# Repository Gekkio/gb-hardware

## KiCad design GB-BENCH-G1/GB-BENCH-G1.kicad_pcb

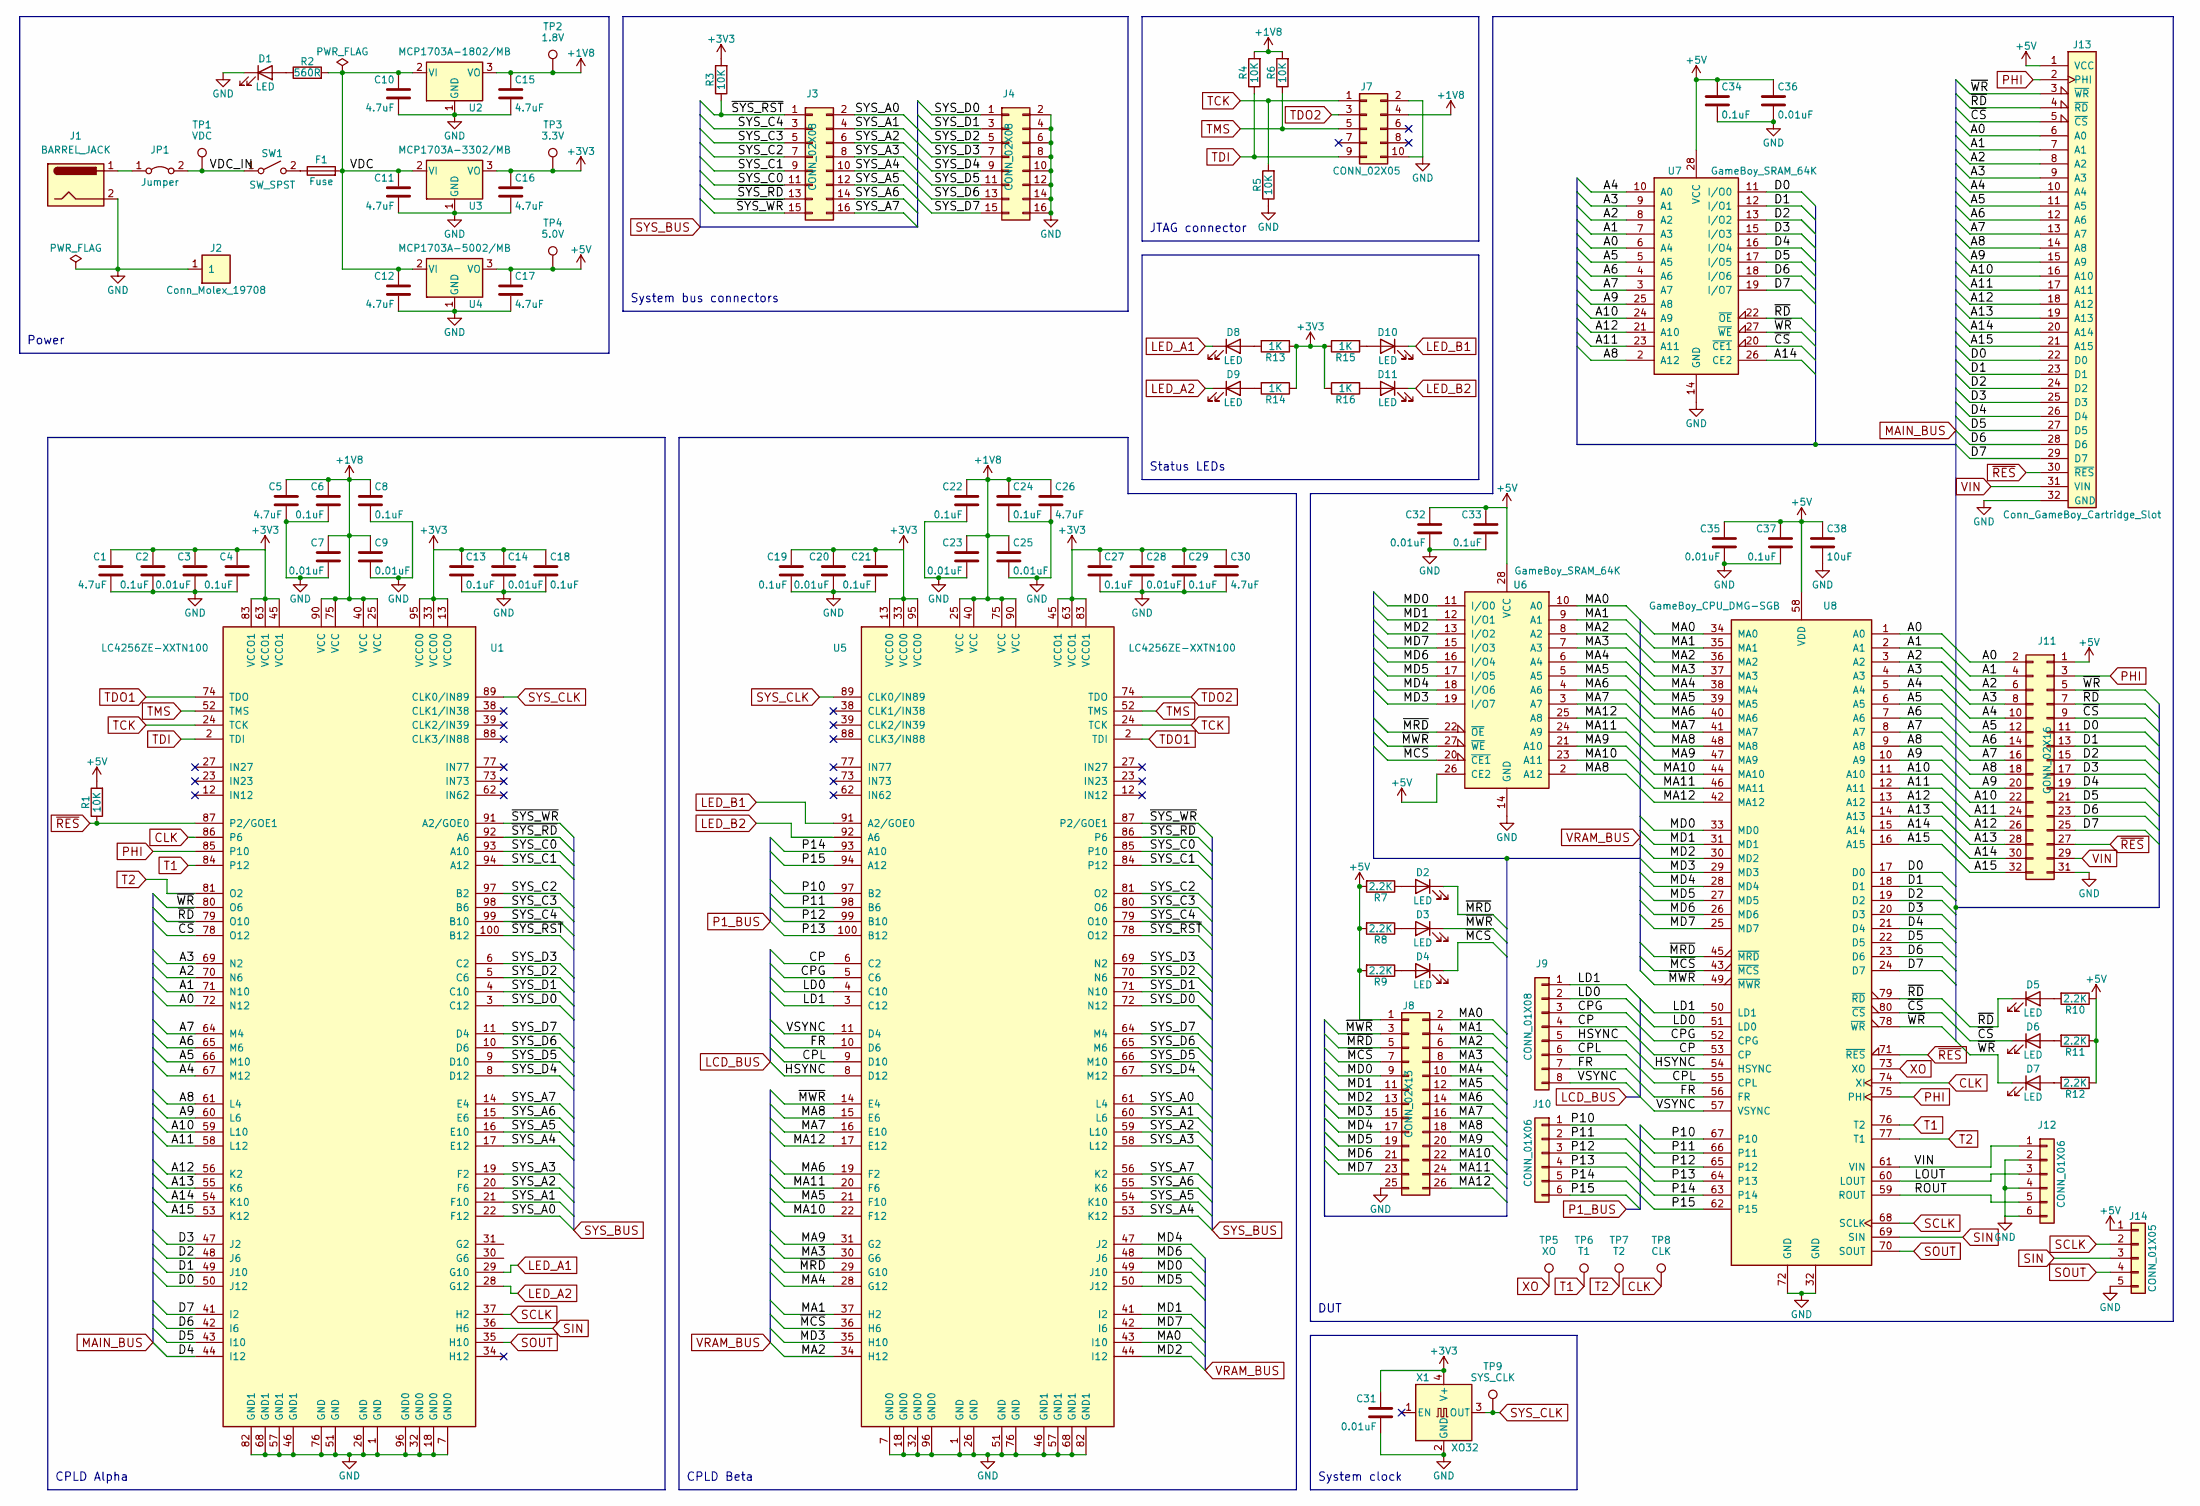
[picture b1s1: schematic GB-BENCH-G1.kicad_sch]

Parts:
C1, C5, C10, C11, C12, C15, C16, C17, C26, C30: 4.7uF; C_1206
C2, C4, C6, C8, C13, C18, C19, C21, C22, C24, C27, C29, C33, C34, C37: 0.1uF; C_0603
C3, C7, C9, C14, C20, C23, C25, C28, C31, C32, C35, C36: 0.01uF; C_0603
C38: 10uF; C_0805
D1: LED; LED_D3.0mm
D2, D3, D4, D5, D6, D7, D8, D9, D10, D11: LED; LED_0603
F1: Fuse; Fuse_SMD1206_Reflow
J1: BARREL_JACK; CUIInc_PJ-202A
J2: Conn_Molex_19708; Molex_19708-401X
J3, J4: CONN_02X08; IDC_Header_Straight_16pins
J7: CONN_02X05; Pin_Header_Straight_2x05_Pitch2.54mm
J8: CONN_02X13; Pin_Header_Straight_2x13_Pitch2.54mm
J9: CONN_01X08; Pin_Header_Straight_1x08_Pitch2.54mm
J10, J12: CONN_01X06; Pin_Header_Straight_1x06_Pitch2.54mm
J11: CONN_02X16; Pin_Header_Straight_2x16_Pitch2.54mm
J13: Conn_GameBoy_Cartridge_Slot; GameBoy_Cartridge_Slot_DSLite
J14: CONN_01X05; Pin_Header_Straight_1x05_Pitch2.54mm
JP1: Jumper; Pin_Header_Straight_1x02_Pitch2.54mm
R1, R3, R4, R5, R6: 10K; R_0603
R2: 560R; R_Axial_DIN0207_L6.3mm_D2.5mm_P7.62mm_Horizontal
R7, R8, R9, R10, R11, R12: 2.2K; R_0603
R13, R14, R15, R16: 1K; R_0603
SW1: SW_SPST; E-Switch_RA12131100
TP1: VDC; PINTST
TP2: 1.8V; PINTST
TP3: 3.3V; PINTST
TP4: 5.0V; PINTST
TP5: XO; PINTST
TP6: T1; PINTST
TP7: T2; PINTST
TP8: CLK; PINTST
TP9: SYS_CLK; PINTST
U1, U5: LC4256ZE-XXTN100; TQFP-100_14x14mm_Pitch0.5mm
U2: MCP1703A-1802/MB; SOT-89-3
U3: MCP1703A-3302/MB; SOT-89-3
U4: MCP1703A-5002/MB; SOT-89-3
U6, U7: GameBoy_SRAM_64K; SOP-28_8.6x18mm_Pitch1.27mm
U8: GameBoy_CPU_DMG-SGB; PQFP-80_14x20mm_Pitch0.8mm
X1: XO32; Oscillator_SMD_EuroQuartz_XO32-4pin_3.2x2.5mm

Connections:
+1V8: C5.1, C6.1, C7.1, C8.1, C9.1, C15.1, C22.1, C23.1, C24.1, C25.1, C26.1, J7.4, R4.2, R6.2, TP2.1, U1.25 (VCC), U1.40 (VCC), U1.75 (VCC), U1.90 (VCC), U2.3 (VO), U5.25 (VCC), U5.40 (VCC), U5.75 (VCC), U5.90 (VCC)
+3V3: C1.1, C2.1, C3.1, C4.1, C13.1, C14.1, C16.1, C18.1, C19.1, C20.1, C21.1, C27.1, C28.1, C29.1, C30.1, C31.1, R3.2, R13.1, R14.1, R15.1, R16.1, TP3.1, U1.13 (VCCO0), U1.33 (VCCO0), U1.45 (VCCO1), U1.63 (VCCO1), U1.83 (VCCO1), U1.95 (VCCO0), U3.3 (VO), U5.13 (VCCO0), U5.33 (VCCO0), U5.45 (VCCO1), U5.63 (VCCO1), U5.83 (VCCO1), U5.95 (VCCO0), X1.4 (V+)
+5V: C17.1, C32.1, C33.1, C34.1, C35.1, C36.1, C37.1, C38.1, J8.1, J11.1, J13.1 (VCC), J14.1, R1.2, R7.2, R8.2, R9.2, R10.1, R11.1, R12.1, TP4.1, U4.3 (VO), U6.26 (CE2), U6.28 (VCC), U7.28 (VCC), U8.58 (VDD)
/A0: J11.2, J13.6 (A0), U1.72 (N12), U7.6 (A4), U8.1 (A0)
/A1: J11.4, J13.7 (A1), U1.71 (N10), U7.7 (A3), U8.2 (A1)
/A2: J11.6, J13.8 (A2), U1.70 (N6), U7.8 (A2), U8.3 (A2)
/A3: J11.8, J13.9 (A3), U1.69 (N2), U7.9 (A1), U8.4 (A3)
/A4: J11.10, J13.10 (A4), U1.67 (M12), U7.10 (A0), U8.5 (A4)
/A5: J11.12, J13.11 (A5), U1.66 (M10), U7.5 (A5), U8.6 (A5)
/A6: J11.14, J13.12 (A6), U1.65 (M6), U7.4 (A6), U8.7 (A6)
/A7: J11.16, J13.13 (A7), U1.64 (M4), U7.3 (A7), U8.8 (A7)
/A8: J11.18, J13.14 (A8), U1.61 (L4), U7.2 (A12), U8.9 (A8)
/A9: J11.20, J13.15 (A9), U1.60 (L6), U7.25 (A8), U8.10 (A9)
/A10: J11.22, J13.16 (A10), U1.59 (L10), U7.24 (A9), U8.11 (A10)
/A11: J11.24, J13.17 (A11), U1.58 (L12), U7.23 (A11), U8.12 (A11)
/A12: J11.26, J13.18 (A12), U1.56 (K2), U7.21 (A10), U8.13 (A12)
/A13: J11.28, J13.19 (A13), U1.55 (K6), U8.14 (A13)
/A14: J11.30, J13.20 (A14), U1.54 (K10), U7.26 (CE2), U8.15 (A14)
/A15: J11.32, J13.21 (A15), U1.53 (K12), U8.16 (A15)
/CP: J9.4, U5.6 (C2), U8.53 (CP)
/CPG: J9.3, U5.5 (C6), U8.52 (CPG)
/CPL: J9.6, U5.9 (D10), U8.55 (CPL)
/D0: J11.11, J13.22 (D0), U1.50 (J12), U7.11 (I/O0), U8.17 (D0)
/D1: J11.13, J13.23 (D1), U1.49 (J10), U7.12 (I/O1), U8.18 (D1)
/D2: J11.15, J13.24 (D2), U1.48 (J6), U7.13 (I/O2), U8.19 (D2)
/D3: J11.17, J13.25 (D3), U1.47 (J2), U7.15 (I/O3), U8.20 (D3)
/D4: J11.19, J13.26 (D4), U1.44 (I12), U7.16 (I/O4), U8.21 (D4)
/D5: J11.21, J13.27 (D5), U1.43 (I10), U7.17 (I/O5), U8.22 (D5)
/D6: J11.23, J13.28 (D6), U1.42 (I6), U7.18 (I/O6), U8.23 (D6)
/D7: J11.25, J13.29 (D7), U1.41 (I2), U7.19 (I/O7), U8.24 (D7)
/FR: J9.7, U5.10 (D6), U8.56 (FR)
/HSYNC: J9.5, U5.8 (D12), U8.54 (HSYNC)
/LD0: J9.2, U5.4 (C10), U8.51 (LD0)
/LD1: J9.1, U5.3 (C12), U8.50 (LD1)
/LOUT: J12.3, U8.60 (LOUT)
/MA0: J8.2, U5.43 (I10), U6.10 (A0), U8.34 (MA0)
/MA1: J8.4, U5.37 (H2), U6.9 (A1), U8.35 (MA1)
/MA2: J8.6, U5.34 (H12), U6.8 (A2), U8.36 (MA2)
/MA3: J8.8, U5.30 (G6), U6.7 (A3), U8.37 (MA3)
/MA4: J8.10, U5.28 (G12), U6.6 (A4), U8.38 (MA4)
/MA5: J8.12, U5.21 (F10), U6.5 (A5), U8.39 (MA5)
/MA6: J8.14, U5.19 (F2), U6.4 (A6), U8.40 (MA6)
/MA7: J8.16, U5.16 (E10), U6.3 (A7), U8.41 (MA7)
/MA8: J8.18, U5.15 (E6), U6.2 (A12), U8.48 (MA8)
/MA9: J8.20, U5.31 (G2), U6.21 (A10), U8.47 (MA9)
/MA10: J8.22, U5.22 (F12), U6.23 (A11), U8.44 (MA10)
/MA11: J8.24, U5.20 (F6), U6.24 (A9), U8.46 (MA11)
/MA12: J8.26, U5.17 (E12), U6.25 (A8), U8.42 (MA12)
/MD0: J8.9, U5.49 (J10), U6.11 (I/O0), U8.33 (MD0)
/MD1: J8.11, U5.41 (I2), U6.12 (I/O1), U8.31 (MD1)
/MD2: J8.13, U5.44 (I12), U6.13 (I/O2), U8.30 (MD2)
/MD3: J8.15, U5.35 (H10), U6.19 (I/O7), U8.29 (MD3)
/MD4: J8.17, U5.47 (J2), U6.18 (I/O6), U8.28 (MD4)
/MD5: J8.19, U5.50 (J12), U6.17 (I/O5), U8.27 (MD5)
/MD6: J8.21, U5.48 (J6), U6.16 (I/O4), U8.26 (MD6)
/MD7: J8.23, U5.42 (I6), U6.15 (I/O3), U8.25 (MD7)
/P10: J10.1, U5.97 (B2), U8.67 (P10)
/P11: J10.2, U5.98 (B6), U8.66 (P11)
/P12: J10.3, U5.99 (B10), U8.65 (P12)
/P13: J10.4, U5.100 (B12), U8.64 (P13)
/P14: J10.5, U5.93 (A10), U8.63 (P14)
/P15: J10.6, U5.94 (A12), U8.62 (P15)
/ROUT: J12.5, U8.59 (ROUT)
/SYS_A0: J3.2, U1.22 (F12), U5.61 (L4)
/SYS_A1: J3.4, U1.21 (F10), U5.60 (L6)
/SYS_A2: J3.6, U1.20 (F6), U5.59 (L10)
/SYS_A3: J3.8, U1.19 (F2), U5.58 (L12)
/SYS_A4: J3.10, U1.17 (E12), U5.53 (K12)
/SYS_A5: J3.12, U1.16 (E10), U5.54 (K10)
/SYS_A6: J3.14, U1.15 (E6), U5.55 (K6)
/SYS_A7: J3.16, U1.14 (E4), U5.56 (K2)
/SYS_C0: J3.11, U1.93 (A10), U5.85 (P10)
/SYS_C1: J3.9, U1.94 (A12), U5.84 (P12)
/SYS_C2: J3.7, U1.97 (B2), U5.81 (O2)
/SYS_C3: J3.5, U1.98 (B6), U5.80 (O6)
/SYS_C4: J3.3, U1.99 (B10), U5.79 (O10)
/SYS_D0: J4.1, U1.3 (C12), U5.72 (N12)
/SYS_D1: J4.3, U1.4 (C10), U5.71 (N10)
/SYS_D2: J4.5, U1.5 (C6), U5.70 (N6)
/SYS_D3: J4.7, U1.6 (C2), U5.69 (N2)
/SYS_D4: J4.9, U1.8 (D12), U5.67 (M12)
/SYS_D5: J4.11, U1.9 (D10), U5.66 (M10)
/SYS_D6: J4.13, U1.10 (D6), U5.65 (M6)
/SYS_D7: J4.15, U1.11 (D4), U5.64 (M4)
/VDC: C10.1, C11.1, C12.1, F1.2, R2.2, U2.2 (VI), U3.2 (VI), U4.2 (VI)
/VDC_IN: JP1.2 (B), SW1.1 (A), TP1.1
/VSYNC: J9.8, U5.11 (D4), U8.57 (VSYNC)
/~CS: D6.1 (K), J11.9, J13.5 (~CS), U1.78 (O12), U7.20 (~CE1), U8.80 (~CS)
/~MCS: D4.1 (K), J8.7, U5.36 (H6), U6.20 (~CE1), U8.43 (~MCS)
/~MRD: D2.1 (K), J8.5, U5.29 (G10), U6.22 (~OE), U8.45 (~MRD)
/~MWR: D3.1 (K), J8.3, U5.14 (E4), U6.27 (~WE), U8.49 (~MWR)
/~RD: D5.1 (K), J11.7, J13.4 (~RD), U1.79 (O10), U7.22 (~OE), U8.79 (~RD)
/~SYS_RD: J3.13, U1.92 (A6), U5.86 (P6)
/~SYS_RST: J3.1, R3.1, U1.100 (B12), U5.78 (O12)
/~SYS_WR: J3.15, U1.91 (A2/GOE0), U5.87 (P2/GOE1)
/~WR: D7.1 (K), J11.5, J13.3 (~WR), U1.80 (O6), U7.27 (~WE), U8.78 (~WR)
CLK: TP8.1, U1.86 (P6), U8.74 (XI)
GND: C1.2, C2.2, C3.2, C4.2, C5.2, C6.2, C7.2, C8.2, C9.2, C10.2, C11.2, C12.2, C13.2, C14.2, C15.2, C16.2, C17.2, C18.2, C19.2, C20.2, C21.2, C22.2, C23.2, C24.2, C25.2, C26.2, C27.2, C28.2, C29.2, C30.2, C31.2, C32.2, C33.2, C34.2, C35.2, C36.2, C37.2, C38.2, D1.1 (K), J1.2, J1.3, J2.1, J4.2, J4.4, J4.6, J4.8, J4.10, J4.12, J4.14, J4.16, J7.2, J7.10, J8.25, J11.31, J12.2, J12.4, J12.6, J13.32 (GND), J14.5, R5.1, U1.1 (GND), U1.7 (GND0), U1.18 (GND0), U1.26 (GND), U1.32 (GND0), U1.46 (GND1), U1.51 (GND), U1.57 (GND1), U1.68 (GND1), U1.76 (GND), U1.82 (GND1), U1.96 (GND0), U2.1 (GND), U3.1 (GND), U4.1 (GND), U5.1 (GND), U5.7 (GND0), U5.18 (GND0), U5.26 (GND), U5.32 (GND0), U5.46 (GND1), U5.51 (GND), U5.57 (GND1), U5.68 (GND1), U5.76 (GND), U5.82 (GND1), U5.96 (GND0), U6.14 (GND), U7.14 (GND), U8.32 (GND), U8.72 (GND), X1.2 (GND)
LED_A1: D8.1 (K), U1.29 (G10)
LED_A2: D9.1 (K), U1.28 (G12)
LED_B1: D10.1 (K), U5.91 (A2/GOE0)
LED_B2: D11.1 (K), U5.92 (A6)
unnamed: D1.2 (A), R2.1
unnamed: D2.2 (A), R7.1
unnamed: D3.2 (A), R8.1
unnamed: D4.2 (A), R9.1
unnamed: D5.2 (A), R10.2
unnamed: D6.2 (A), R11.2
unnamed: D7.2 (A), R12.2
unnamed: D8.2 (A), R13.2
unnamed: D9.2 (A), R14.2
unnamed: D10.2 (A), R15.2
unnamed: D11.2 (A), R16.2
unnamed: F1.1, SW1.2 (B)
unnamed: J1.1, JP1.1 (A)
PHI: J11.3, J13.2 (PHI), U1.85 (P10), U8.75 (PHI)
SCLK: J14.2, U1.37 (H2), U8.68 (SCLK)
SIN: J14.3, U1.36 (H6), U8.69 (SIN)
SOUT: J14.4, U1.35 (H10), U8.70 (SOUT)
SYS_CLK: TP9.1, U1.89 (CLK0/IN89), U5.89 (CLK0/IN89), X1.3 (OUT)
T1: TP6.1, U1.84 (P12), U8.76 (T2)
T2: TP7.1, U1.81 (O2), U8.77 (T1)
TCK: J7.1, R5.2, U1.24 (TCK), U5.24 (TCK)
TDI: J7.9, R4.1, U1.2 (TDI)
TDO1: U1.74 (TDO), U5.2 (TDI)
TDO2: J7.3, U5.74 (TDO)
TMS: J7.5, R6.1, U1.52 (TMS), U5.52 (TMS)
VIN: J11.29, J12.1, J13.31 (VIN), U8.61 (VIN)
XO: TP5.1, U8.73 (XO)
~RES: J11.27, J13.30 (~RES), R1.1, U1.87 (P2/GOE1), U8.71 (~RES)

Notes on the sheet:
Status LEDs
JTAG connector
CPLD Alpha
System clock
Power
CPLD Beta
System bus connectors
DUT

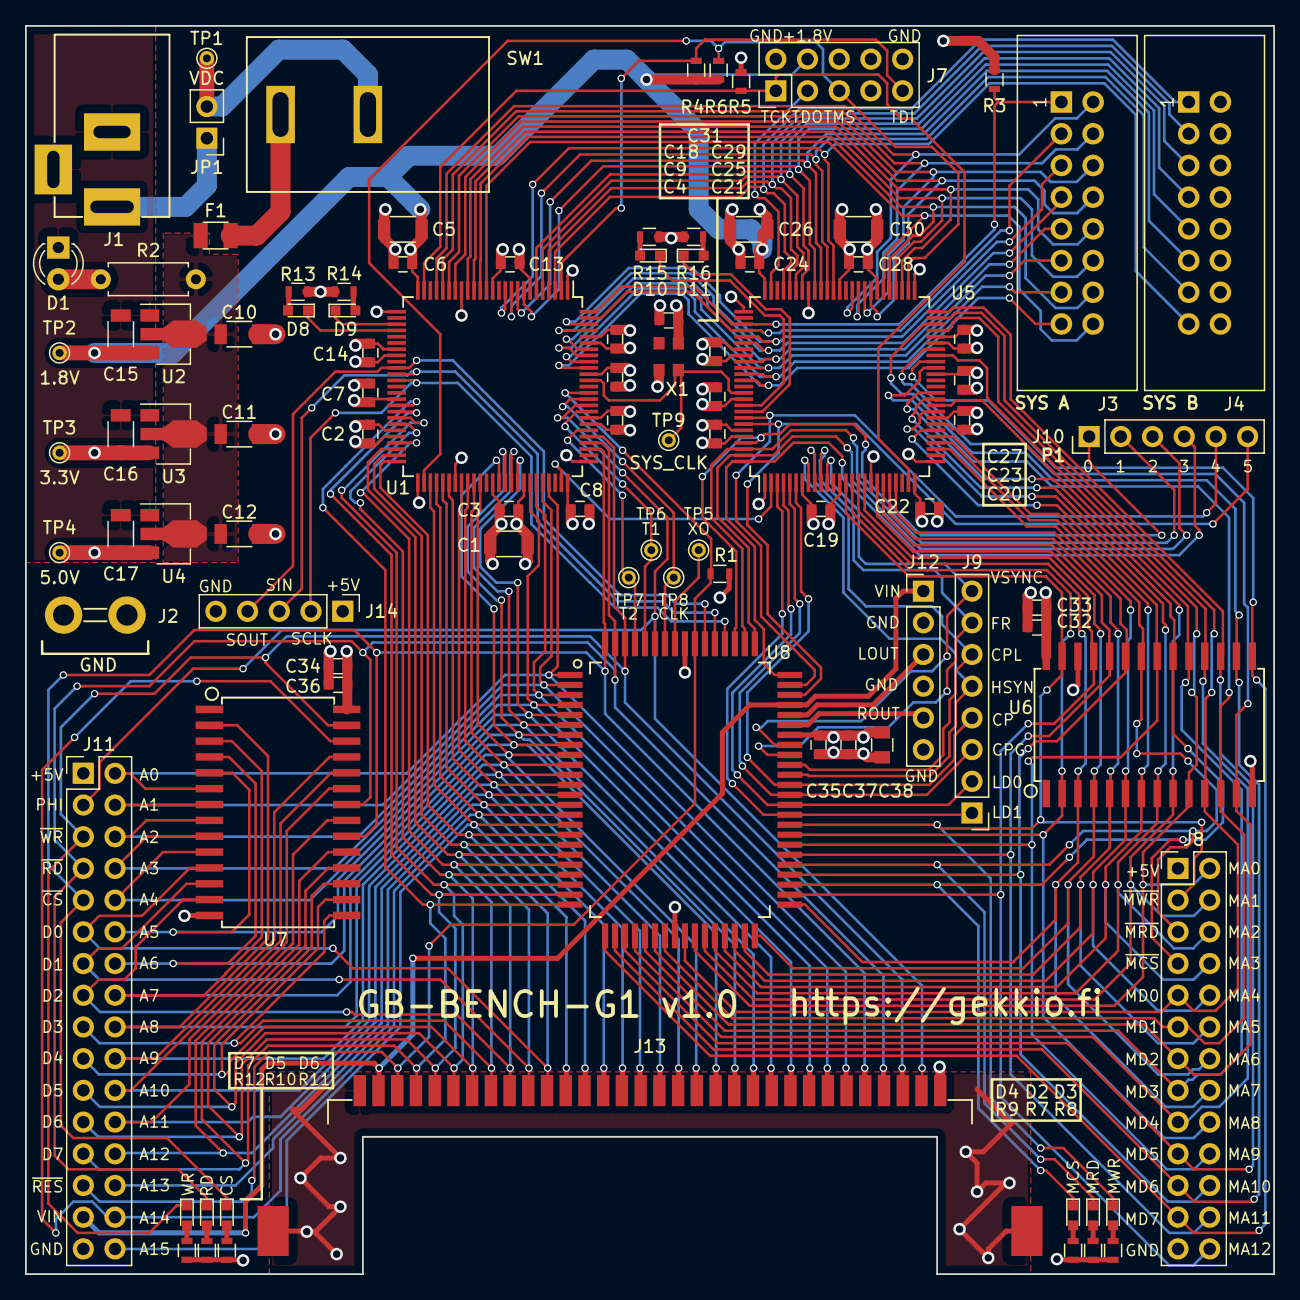
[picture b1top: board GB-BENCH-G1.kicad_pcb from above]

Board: 4 copper layers, 100.0 x 100.0 mm, 98 parts (0 on the bottom side), 130 nets.

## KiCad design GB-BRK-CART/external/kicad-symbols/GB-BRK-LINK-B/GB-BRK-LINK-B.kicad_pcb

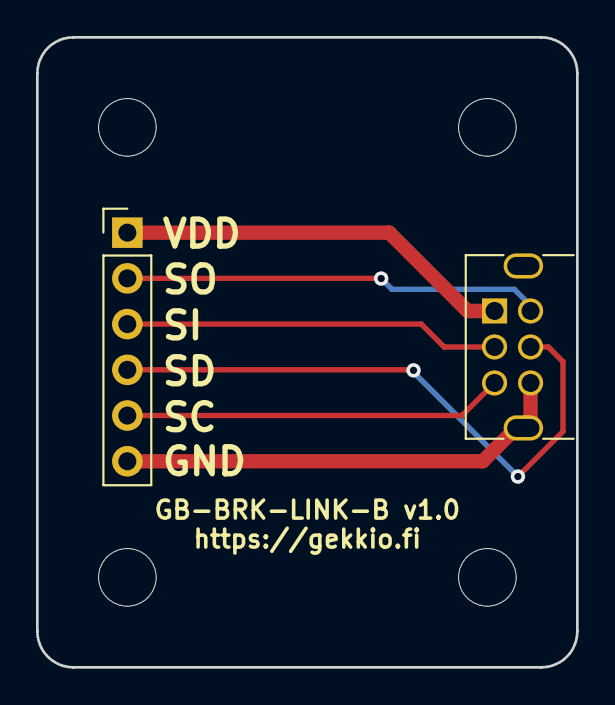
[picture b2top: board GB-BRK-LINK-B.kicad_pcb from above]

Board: 2 copper layers, 30.0 x 35.0 mm, 6 parts (0 on the bottom side), 6 nets.

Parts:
H1, H2, H3, H4: DNF; MountingHole_3.2mm_M3
J1: Conn_01x06; PinHeader_1x06_P2.54mm_Vertical
J2: GameBoy_LinkPort; GameBoy_LinkPort_MGB_Horizontal

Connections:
/GND: J1.6, J2.6, J2.SH
unnamed: J1.1, J2.1
unnamed: J1.2, J2.2
unnamed: J1.3, J2.3
unnamed: J1.4, J2.4
unnamed: J1.5, J2.5

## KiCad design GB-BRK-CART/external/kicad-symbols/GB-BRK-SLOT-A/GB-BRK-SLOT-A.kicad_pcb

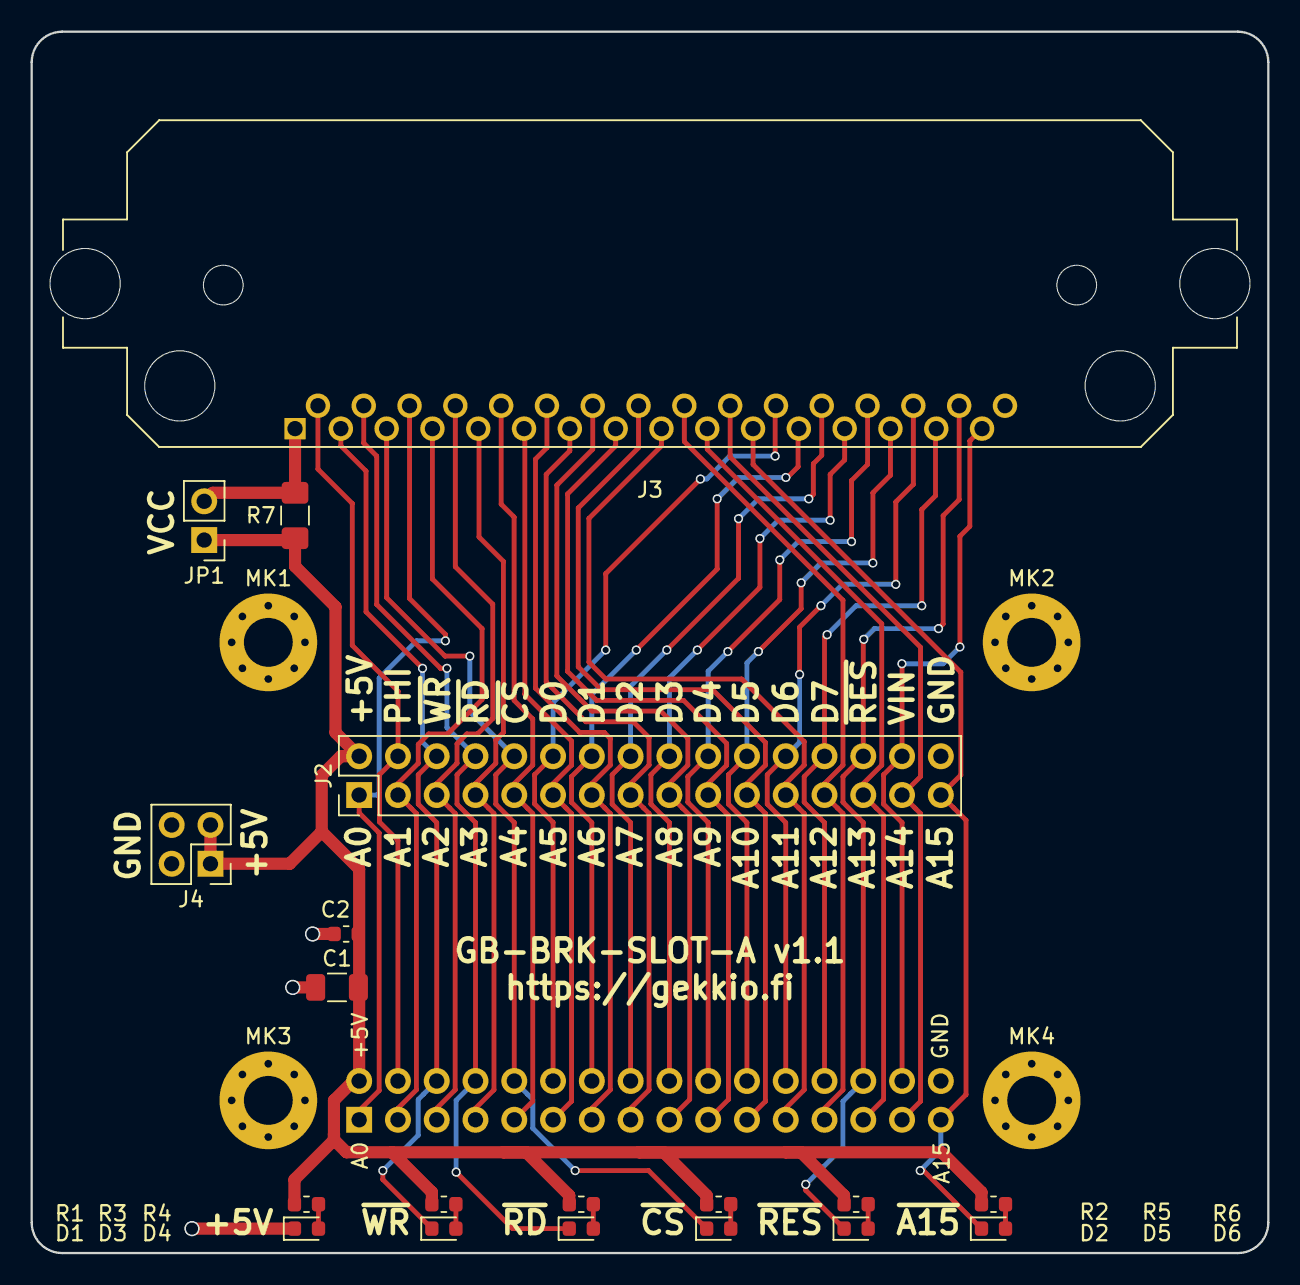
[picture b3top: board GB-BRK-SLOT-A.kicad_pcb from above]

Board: 2 copper layers, 81.0 x 80.0 mm, 24 parts (1 on the bottom side), 39 nets.

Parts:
C1: 10uF; C_1206_3216Metric
C2: 0.1uF; C_0603_1608Metric
D1, D2, D3, D4, D5, D6: LED; LED_0603_1608Metric
J1: Conn_02x16_Odd_Even; PinSocket_2x16_P2.54mm_Vertical
J2: Conn_02x16_Odd_Even; PinHeader_2x16_P2.54mm_Vertical
J3: GameBoy_Cartridge; GameBoy_Cartridge_DMG_1x32_P1.50mm_Socket_Horizontal
J4: Conn_02x02_Odd_Even; PinHeader_2x02_P2.54mm_Vertical
JP1: Jumper_NC_Small; PinHeader_1x02_P2.54mm_Vertical
MK1, MK2, MK3, MK4: MountingHole_Pad; MountingHole_3.2mm_M3_Pad_Via
R1, R2, R3, R4, R5, R6: 3.3k; R_0603_1608Metric
R7: 0R; R_1206_3216Metric_Pad1.42x1.75mm_HandSolder

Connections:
+5V: C1.1, C2.1, J1.2, J2.2, J4.1, J4.3, JP1.1, R1.1, R2.1, R3.1, R4.1, R5.1, R6.1, R7.2
/A0: J1.1, J2.1, J3.6
/A1: J1.3, J2.3, J3.7
/A2: J1.5, J2.5, J3.8
/A3: J1.7, J2.7, J3.9
/A4: J1.9, J2.9, J3.10
/A5: J1.11, J2.11, J3.11
/A6: J1.13, J2.13, J3.12
/A7: J1.15, J2.15, J3.13
/A8: J1.17, J2.17, J3.14
/A9: J1.19, J2.19, J3.15
/A10: J1.21, J2.21, J3.16
/A11: J1.23, J2.23, J3.17
/A12: J1.25, J2.25, J3.18
/A13: J1.27, J2.27, J3.19
/A14: J1.29, J2.29, J3.20
/A15: D6.1, J1.31, J2.31, J3.21
/D0: J1.12, J2.12, J3.22
/D1: J1.14, J2.14, J3.23
/D2: J1.16, J2.16, J3.24
/D3: J1.18, J2.18, J3.25
/D4: J1.20, J2.20, J3.26
/D5: J1.22, J2.22, J3.27
/D6: J1.24, J2.24, J3.28
/D7: J1.26, J2.26, J3.29
/PHI: J1.4, J2.4, J3.2
/VIN: J1.30, J2.30, J3.31
/~CS: D5.1, J1.10, J2.10, J3.5
/~RD: D4.1, J1.8, J2.8, J3.4
/~RES: D2.1, J1.28, J2.28, J3.30
/~WR: D3.1, J1.6, J2.6, J3.3
GND: C1.2, C2.2, D1.1, J1.32, J2.32, J3.32, J4.2, J4.4, MK1.1, MK2.1, MK3.1, MK4.1
unnamed: D1.2, R1.2
unnamed: D2.2, R2.2
unnamed: D3.2, R3.2
unnamed: D4.2, R4.2
unnamed: D5.2, R5.2
unnamed: D6.2, R6.2
unnamed: J3.1, JP1.2, R7.1

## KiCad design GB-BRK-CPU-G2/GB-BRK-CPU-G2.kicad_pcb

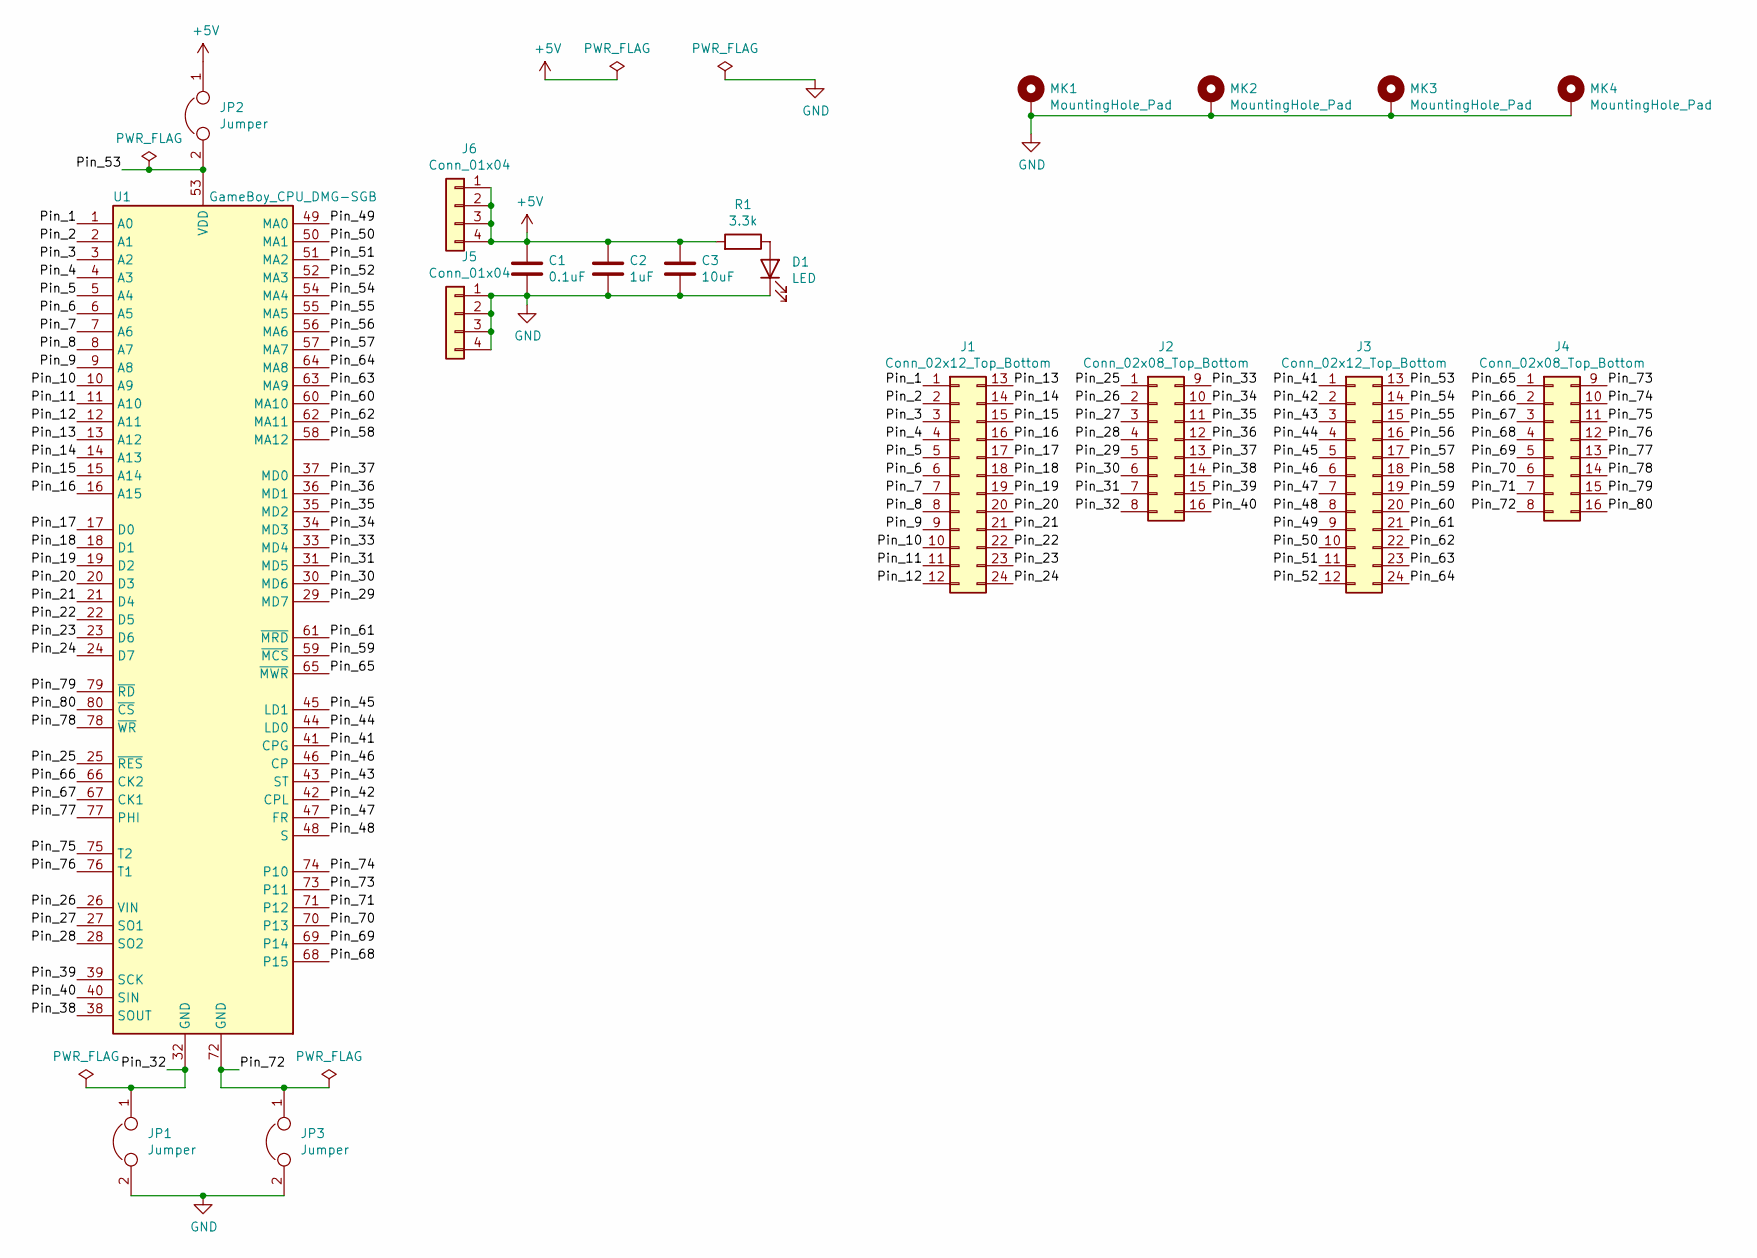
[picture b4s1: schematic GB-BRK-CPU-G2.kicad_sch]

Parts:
C1: 0.1uF; C_0603_1608Metric
C2: 1uF; C_0805_2012Metric
C3: 10uF; C_1206_3216Metric
D1: LED; LED_0603_1608Metric
J1, J3: Conn_02x12_Top_Bottom; PinHeader_2x12_P2.54mm_Vertical
J2, J4: Conn_02x08_Top_Bottom; PinHeader_2x08_P2.54mm_Vertical
J5, J6: Conn_01x04; PinHeader_1x04_P2.54mm_Vertical
JP1, JP2, JP3: Jumper; SolderJumper-2_P1.3mm_Open_TrianglePad1.0x1.5mm
MK1, MK2, MK3, MK4: MountingHole_Pad; MountingHole_3.2mm_M3_Pad_Via
R1: 3.3k; R_0603_1608Metric
U1: GameBoy_CPU_DMG-SGB; Sharp_QFP-80_14x20mm_P0.8mm

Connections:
+5V: C1.1, C2.1, C3.1, J6.1, J6.2, J6.3, J6.4, JP2.1, R1.2
/Pin_1: J1.1, U1.1 (A0)
/Pin_2: J1.2, U1.2 (A1)
/Pin_3: J1.3, U1.3 (A2)
/Pin_4: J1.4, U1.4 (A3)
/Pin_5: J1.5, U1.5 (A4)
/Pin_6: J1.6, U1.6 (A5)
/Pin_7: J1.7, U1.7 (A6)
/Pin_8: J1.8, U1.8 (A7)
/Pin_9: J1.9, U1.9 (A8)
/Pin_10: J1.10, U1.10 (A9)
/Pin_11: J1.11, U1.11 (A10)
/Pin_12: J1.12, U1.12 (A11)
/Pin_13: J1.13, U1.13 (A12)
/Pin_14: J1.14, U1.14 (A13)
/Pin_15: J1.15, U1.15 (A14)
/Pin_16: J1.16, U1.16 (A15)
/Pin_17: J1.17, U1.17 (D0)
/Pin_18: J1.18, U1.18 (D1)
/Pin_19: J1.19, U1.19 (D2)
/Pin_20: J1.20, U1.20 (D3)
/Pin_21: J1.21, U1.21 (D4)
/Pin_22: J1.22, U1.22 (D5)
/Pin_23: J1.23, U1.23 (D6)
/Pin_24: J1.24, U1.24 (D7)
/Pin_25: J2.1, U1.25 (~RES)
/Pin_26: J2.2, U1.26 (VIN)
/Pin_27: J2.3, U1.27 (SO1)
/Pin_28: J2.4, U1.28 (SO2)
/Pin_29: J2.5, U1.29 (MD7)
/Pin_30: J2.6, U1.30 (MD6)
/Pin_31: J2.7, U1.31 (MD5)
/Pin_32: J2.8, JP1.1, U1.32 (GND)
/Pin_33: J2.9, U1.33 (MD4)
/Pin_34: J2.10, U1.34 (MD3)
/Pin_35: J2.11, U1.35 (MD2)
/Pin_36: J2.12, U1.36 (MD1)
/Pin_37: J2.13, U1.37 (MD0)
/Pin_38: J2.14, U1.38 (SOUT)
/Pin_39: J2.15, U1.39 (SCK)
/Pin_40: J2.16, U1.40 (SIN)
/Pin_41: J3.1, U1.41 (CPG)
/Pin_42: J3.2, U1.42 (CPL)
/Pin_43: J3.3, U1.43 (ST)
/Pin_44: J3.4, U1.44 (LD0)
/Pin_45: J3.5, U1.45 (LD1)
/Pin_46: J3.6, U1.46 (CP)
/Pin_47: J3.7, U1.47 (FR)
/Pin_48: J3.8, U1.48 (S)
/Pin_49: J3.9, U1.49 (MA0)
/Pin_50: J3.10, U1.50 (MA1)
/Pin_51: J3.11, U1.51 (MA2)
/Pin_52: J3.12, U1.52 (MA3)
/Pin_53: J3.13, JP2.2, U1.53 (VDD)
/Pin_54: J3.14, U1.54 (MA4)
/Pin_55: J3.15, U1.55 (MA5)
/Pin_56: J3.16, U1.56 (MA6)
/Pin_57: J3.17, U1.57 (MA7)
/Pin_58: J3.18, U1.58 (MA12)
/Pin_59: J3.19, U1.59 (~MCS)
/Pin_60: J3.20, U1.60 (MA10)
/Pin_61: J3.21, U1.61 (~MRD)
/Pin_62: J3.22, U1.62 (MA11)
/Pin_63: J3.23, U1.63 (MA9)
/Pin_64: J3.24, U1.64 (MA8)
/Pin_65: J4.1, U1.65 (~MWR)
/Pin_66: J4.2, U1.66 (CK2)
/Pin_67: J4.3, U1.67 (CK1)
/Pin_68: J4.4, U1.68 (P15)
/Pin_69: J4.5, U1.69 (P14)
/Pin_70: J4.6, U1.70 (P13)
/Pin_71: J4.7, U1.71 (P12)
/Pin_72: J4.8, JP3.1, U1.72 (GND)
/Pin_73: J4.9, U1.73 (P11)
/Pin_74: J4.10, U1.74 (P10)
/Pin_75: J4.11, U1.75 (T2)
/Pin_76: J4.12, U1.76 (T1)
/Pin_77: J4.13, U1.77 (PHI)
/Pin_78: J4.14, U1.78 (~WR)
/Pin_79: J4.15, U1.79 (~RD)
/Pin_80: J4.16, U1.80 (~CS)
GND: C1.2, C2.2, C3.2, D1.1 (K), J5.1, J5.2, J5.3, J5.4, JP1.2, JP3.2, MK1.1, MK2.1, MK3.1, MK4.1
unnamed: D1.2 (A), R1.1

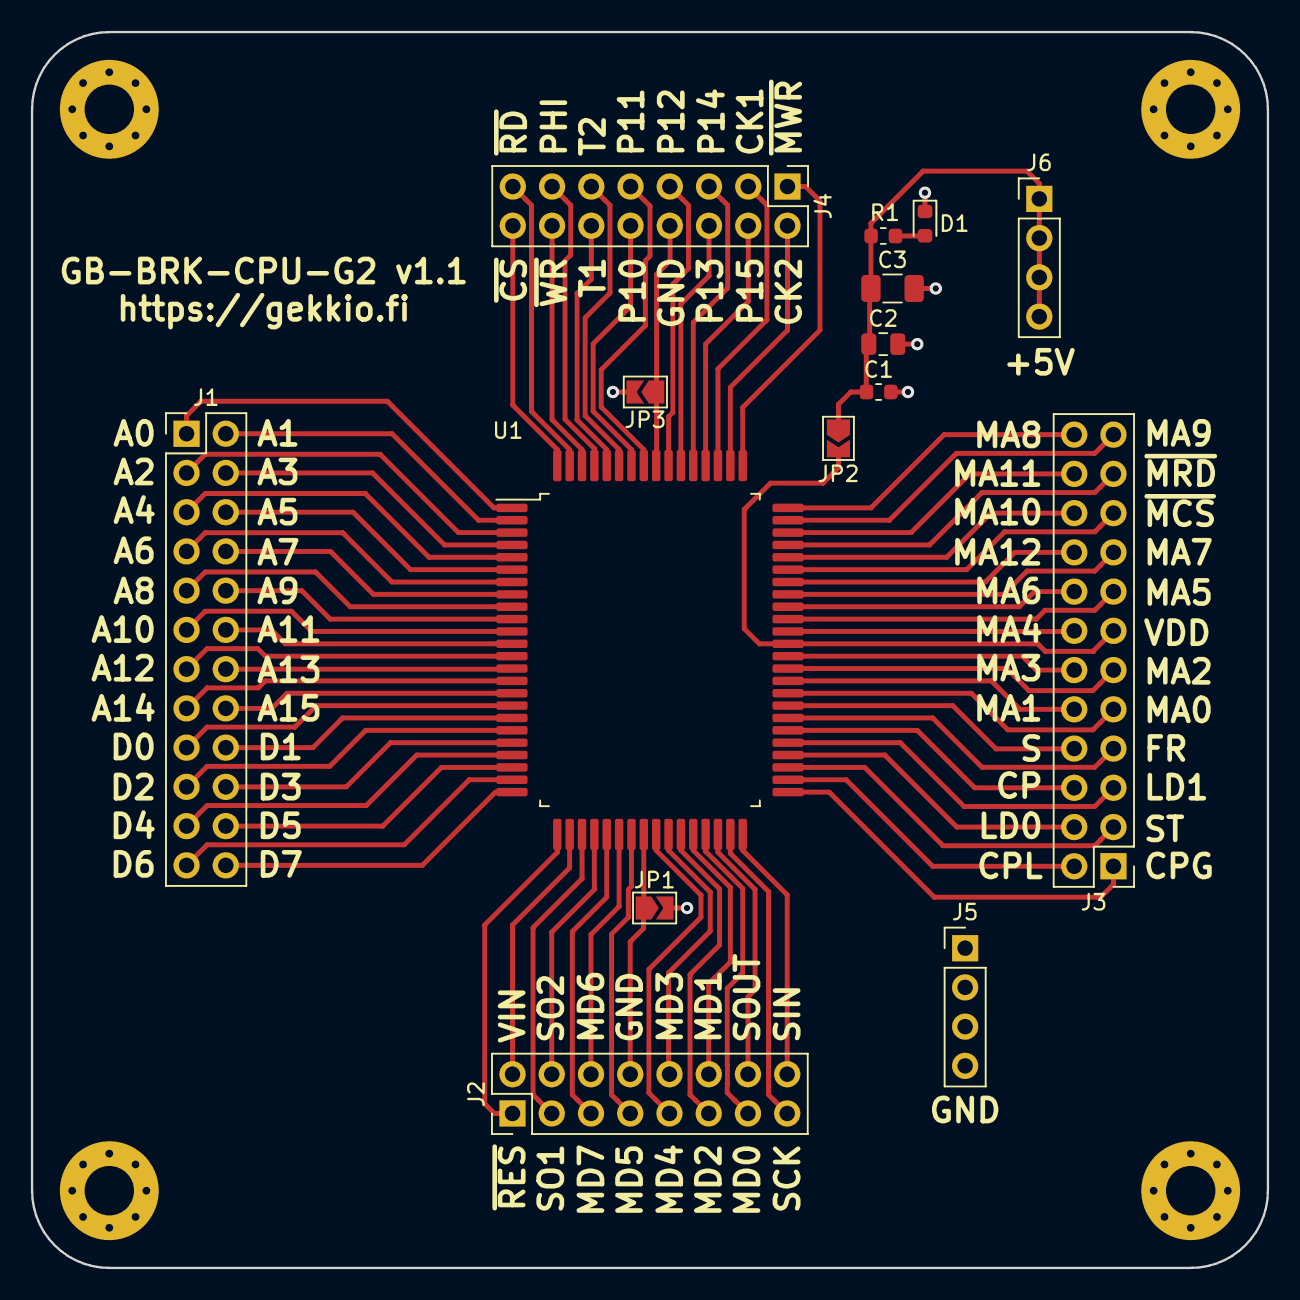
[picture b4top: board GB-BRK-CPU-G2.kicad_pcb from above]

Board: 2 copper layers, 80.0 x 80.0 mm, 19 parts (0 on the bottom side), 83 nets.

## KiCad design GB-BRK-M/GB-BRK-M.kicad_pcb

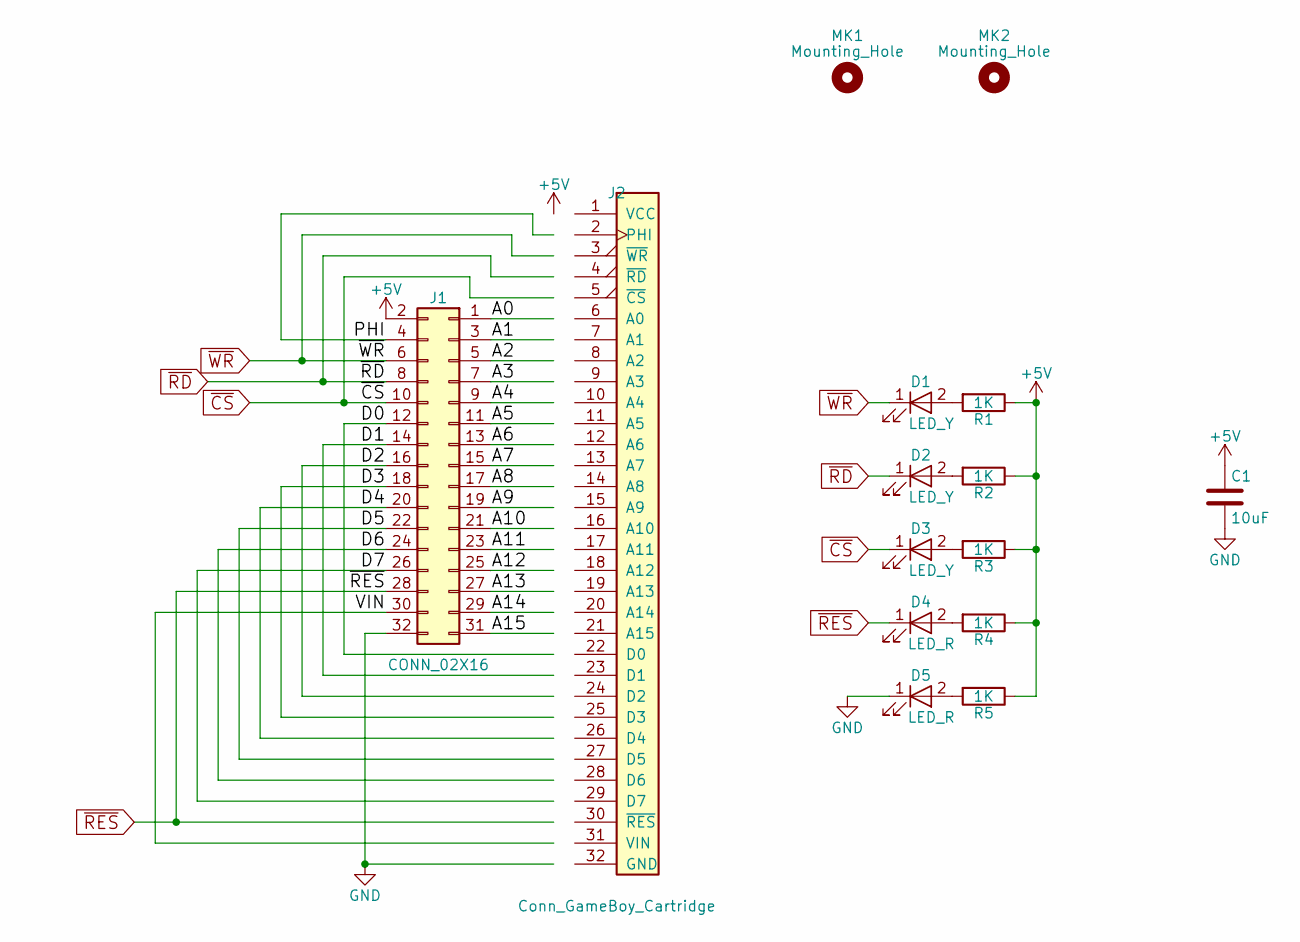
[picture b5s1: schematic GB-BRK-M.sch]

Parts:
C1: 10uF; C_0805_2012Metric; Rating 16V X5R; MPN 0805YD106KAT4A
D1, D2, D3: LED_Y; LED_0603_1608Metric; MPN 150060YS75000
D4, D5: LED_R; LED_0603_1608Metric; MPN 150060SS75000
J1: CONN_02X16; PinHeader_2x16_P2.54mm_Vertical_SMD; MPN 15-91-0400
J2: Conn_GameBoy_Cartridge; GameBoy_Cartridge
MK1, MK2: Mounting_Hole
R1, R2, R3, R4, R5: 1K; R_0603_1608Metric; Rating 1/10W 5%; MPN CRCW06031K00JNEA

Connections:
+5V: C1.1, J1.2, J2.1 (VCC), R1.1, R2.1, R3.1, R4.1, R5.1
/A0: J1.1, J2.6 (A0)
/A1: J1.3, J2.7 (A1)
/A2: J1.5, J2.8 (A2)
/A3: J1.7, J2.9 (A3)
/A4: J1.9, J2.10 (A4)
/A5: J1.11, J2.11 (A5)
/A6: J1.13, J2.12 (A6)
/A7: J1.15, J2.13 (A7)
/A8: J1.17, J2.14 (A8)
/A9: J1.19, J2.15 (A9)
/A10: J1.21, J2.16 (A10)
/A11: J1.23, J2.17 (A11)
/A12: J1.25, J2.18 (A12)
/A13: J1.27, J2.19 (A13)
/A14: J1.29, J2.20 (A14)
/A15: J1.31, J2.21 (A15)
/D0: J1.12, J2.22 (D0)
/D1: J1.14, J2.23 (D1)
/D2: J1.16, J2.24 (D2)
/D3: J1.18, J2.25 (D3)
/D4: J1.20, J2.26 (D4)
/D5: J1.22, J2.27 (D5)
/D6: J1.24, J2.28 (D6)
/D7: J1.26, J2.29 (D7)
/PHI: J1.4, J2.2 (PHI)
/VIN: J1.30, J2.31 (VIN)
GND: C1.2, D5.1 (K), J1.32, J2.32 (GND)
unnamed: D1.2 (A), R1.2
unnamed: D2.2 (A), R2.2
unnamed: D3.2 (A), R3.2
unnamed: D4.2 (A), R4.2
unnamed: D5.2 (A), R5.2
~CS: D3.1 (K), J1.10, J2.5 (~CS)
~RD: D2.1 (K), J1.8, J2.4 (~RD)
~RES: D4.1 (K), J1.28, J2.30 (~RES)
~WR: D1.1 (K), J1.6, J2.3 (~WR)

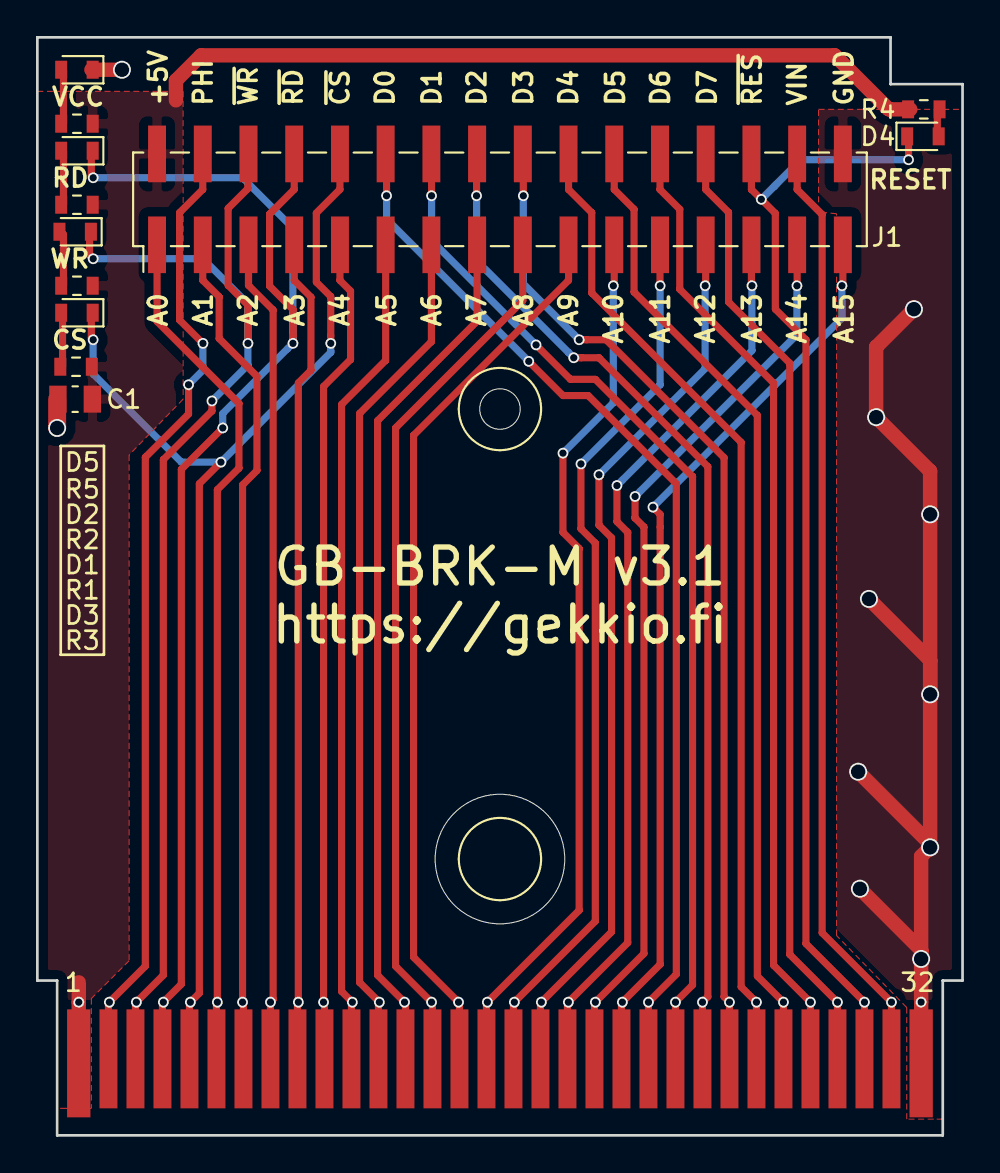
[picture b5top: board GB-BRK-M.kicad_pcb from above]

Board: 2 copper layers, 51.4 x 61.0 mm, 15 parts (0 on the bottom side), 37 nets.
